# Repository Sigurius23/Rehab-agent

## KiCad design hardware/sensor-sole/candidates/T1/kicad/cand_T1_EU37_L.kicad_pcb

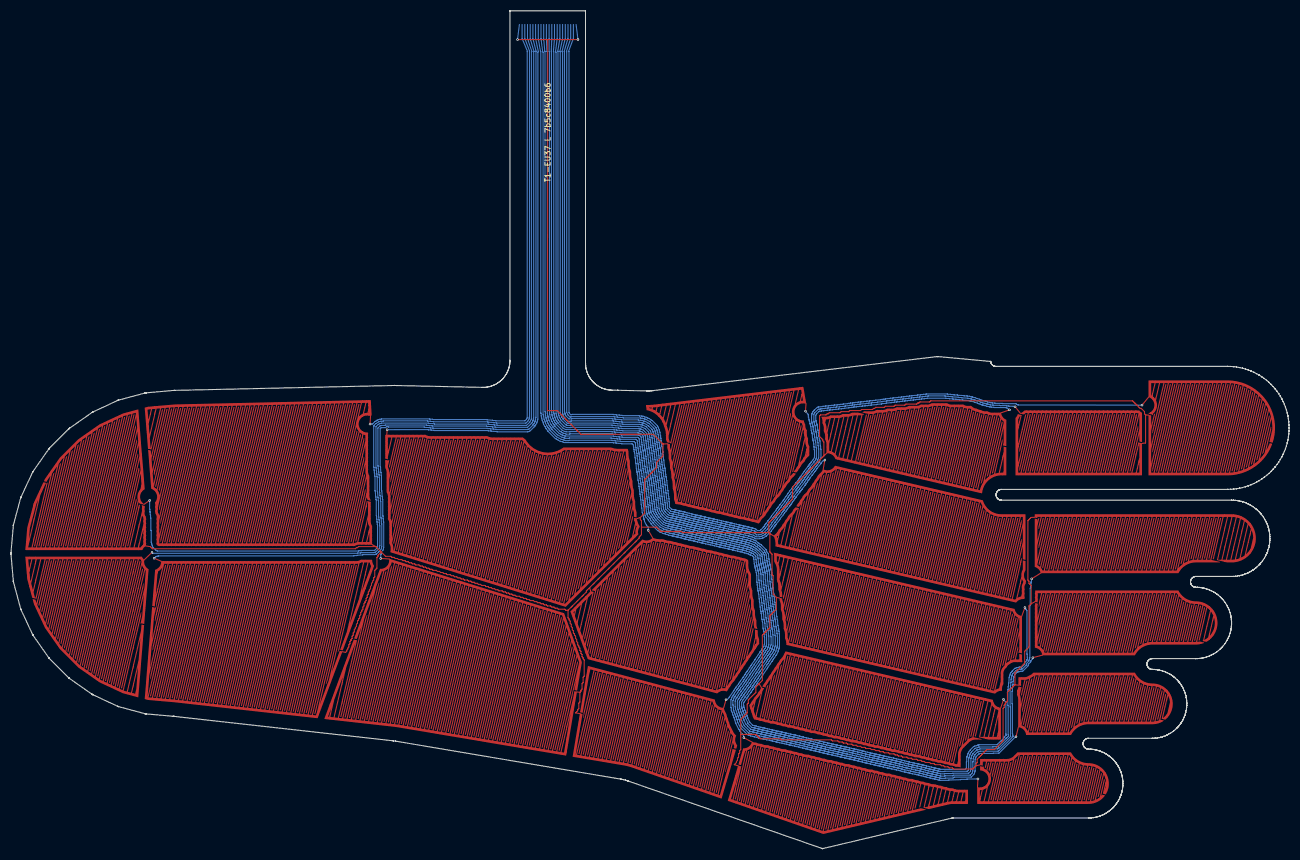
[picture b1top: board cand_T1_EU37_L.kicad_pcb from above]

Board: 2 copper layers, 236.8 x 155.2 mm, 21 parts (0 on the bottom side), 21 nets.

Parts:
J1: FFC 22p 0.5 mm, ZIF, stiffener to 0.3 mm total; ffc_contacts
S01: heel_pm; region
S02: heel_pl; region
S03: heel_am; region
S04: heel_al; region
S05: arch_med; region
S06: mid_lat_prox; region
S07: mid_lat_dist; region
S08: ffp_med; region
S09: ffp_cen; region
S10: mt1; region
S11: mt2; region
S12: mt3; region
S13: mt4; region
S14: mt5; region
S15: toe1_base; region
S16: toe1_tip; region
S17: toe2; region
S18: toe3; region
S19: toe4; region
S20: toe5; region

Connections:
COM: J1.1, J1.22, S01.2, S02.2, S03.2, S04.2, S05.2, S06.2, S07.2, S08.2, S09.2, S10.2, S11.2, S12.2, S13.2, S14.2, S15.2, S16.2, S17.2, S18.2, S19.2, S20.2
S_arch_med: J1.16, S05.1
S_ffp_cen: J1.15, S09.1
S_ffp_med: J1.2, S08.1
S_heel_al: J1.18, S04.1
S_heel_am: J1.21, S03.1
S_heel_pl: J1.19, S02.1
S_heel_pm: J1.20, S01.1
S_mid_lat_dist: J1.14, S07.1
S_mid_lat_prox: J1.17, S06.1
S_mt1: J1.5, S10.1
S_mt2: J1.6, S11.1
S_mt3: J1.8, S12.1
S_mt4: J1.7, S13.1
S_mt5: J1.13, S14.1
S_toe1_base: J1.4, S15.1
S_toe1_tip: J1.3, S16.1
S_toe2: J1.9, S17.1
S_toe3: J1.10, S18.1
S_toe4: J1.11, S19.1
S_toe5: J1.12, S20.1

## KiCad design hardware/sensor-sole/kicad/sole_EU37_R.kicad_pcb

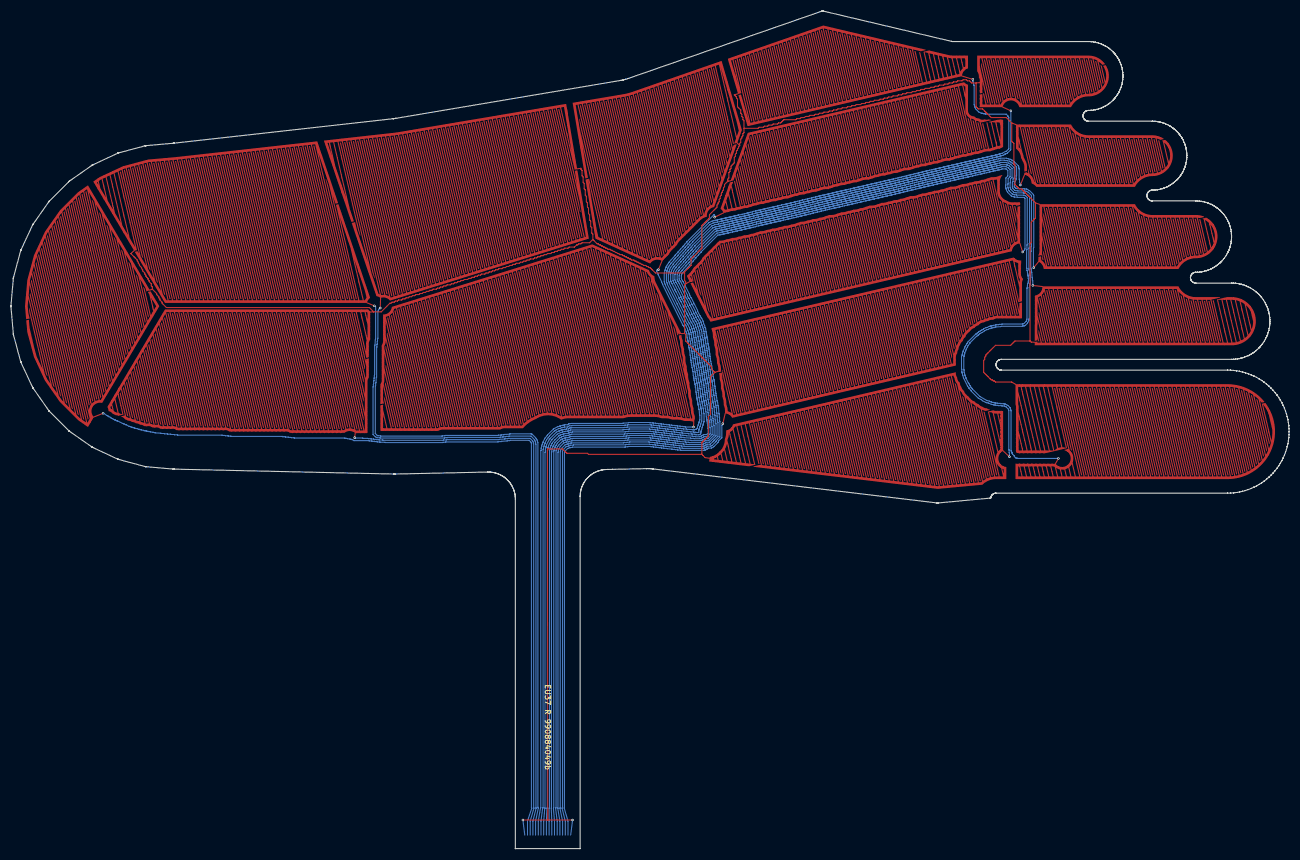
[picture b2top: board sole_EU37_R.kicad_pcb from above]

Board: 2 copper layers, 236.8 x 155.2 mm, 17 parts (0 on the bottom side), 17 nets.

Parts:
J1: FFC 18p 0.5 mm, ZIF, stiffener to 0.3 mm total; ffc_contacts
S01: heel_post; region
S02: heel_med; region
S03: heel_lat; region
S04: arch_med; region
S05: mid_lat_prox; region
S06: mid_lat_dist; region
S07: mt1; region
S08: mt2; region
S09: mt3; region
S10: mt4; region
S11: mt5; region
S12: toe1; region
S13: toe2; region
S14: toe3; region
S15: toe4; region
S16: toe5; region

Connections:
COM: J1.1, J1.18, S01.2, S02.2, S03.2, S04.2, S05.2, S06.2, S07.2, S08.2, S09.2, S10.2, S11.2, S12.2, S13.2, S14.2, S15.2, S16.2
S_arch_med: J1.6, S04.1
S_heel_lat: J1.4, S03.1
S_heel_med: J1.3, S02.1
S_heel_post: J1.2, S01.1
S_mid_lat_dist: J1.7, S06.1
S_mid_lat_prox: J1.5, S05.1
S_mt1: J1.15, S07.1
S_mt2: J1.17, S08.1
S_mt3: J1.16, S09.1
S_mt4: J1.8, S10.1
S_mt5: J1.9, S11.1
S_toe1: J1.14, S12.1
S_toe2: J1.13, S13.1
S_toe3: J1.12, S14.1
S_toe4: J1.11, S15.1
S_toe5: J1.10, S16.1

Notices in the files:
hardware/sensor-sole/candidates/T1/kicad/cand_T1_EU37_L.kicad_pcb:
CERN-OHL-S-2.0
CERN-OHL-S-2.0  Source: https://github.com/Sigurius23/Rehab-agent/tree/main/hardware/sensor-sole
